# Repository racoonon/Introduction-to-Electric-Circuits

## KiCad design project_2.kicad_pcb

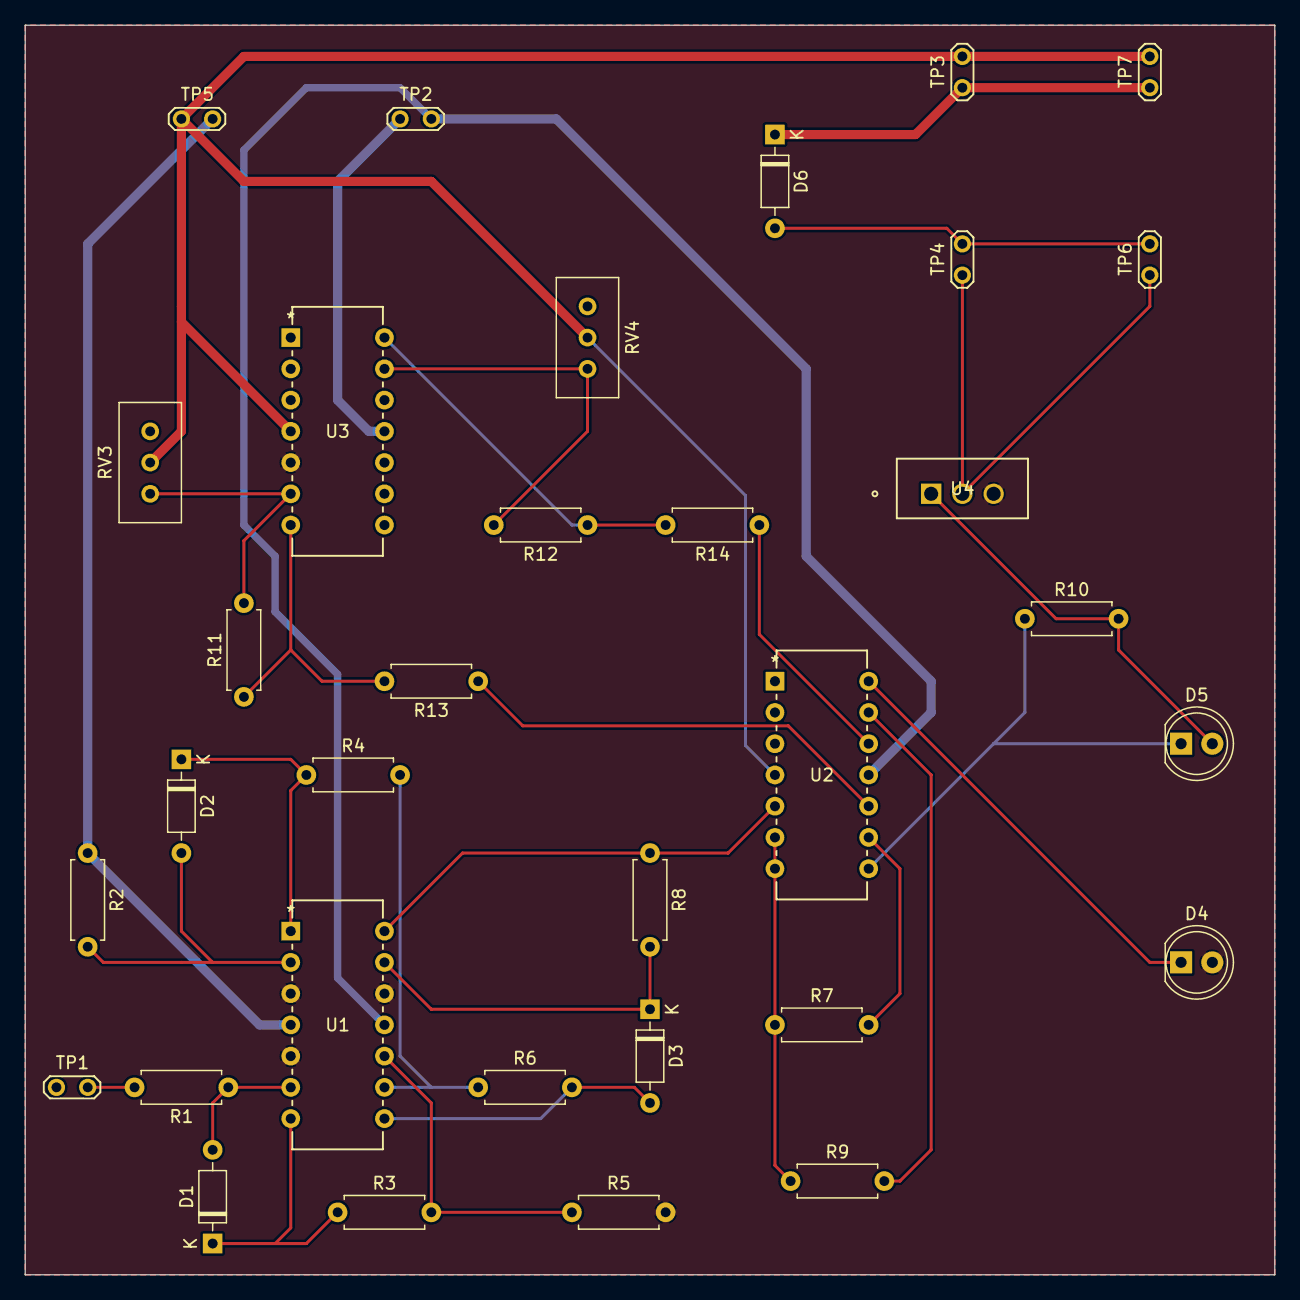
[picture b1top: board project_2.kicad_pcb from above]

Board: 2 copper layers, 101.6 x 101.6 mm, 33 parts (0 on the bottom side), 27 nets.

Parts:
D1, D2, D3, D6: 1N4148; D_DO-35_SOD27_P7.62mm_Horizontal
D4, D5: LED; LED_D5.0mm
R1, R2, R3, R4, R5, R7, R9, R10: 1.1k; R_Axial_DIN0207_L6.3mm_D2.5mm_P7.62mm_Horizontal
R6: 2.2k; R_Axial_DIN0207_L6.3mm_D2.5mm_P7.62mm_Horizontal
R8: 11k; R_Axial_DIN0207_L6.3mm_D2.5mm_P7.62mm_Horizontal
R11, R12, R13, R14: R; R_Axial_DIN0207_L6.3mm_D2.5mm_P7.62mm_Horizontal
RV3, RV4: R_Potentiometer; Potentiometer_Bourns_3296W_Vertical
TP1, TP2, TP3, TP4, TP5, TP6, TP7: TestPoint_2Pole; TestPoint_2Pads_Pitch2.54mm_Drill0.8mm
U1, U2, U3: LM324N; DIP-14_STM
U4: TIP120; TO-220_STM

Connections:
GND: D4.2 (A), R5.2, U1.3 (IN+), U1.5 (IN+), U1.12 (IN+), U3.5 (IN+), U4.3
unnamed: D1.2 (A), R1.1, U1.6 (IN-)
unnamed: D1.1 (K), R3.1, U1.7 (OUT)
unnamed: D2.2 (A), R2.2, U1.2 (IN-)
unnamed: D2.1 (K), R4.1, U1.1 (OUT)
unnamed: D3.2 (A), R6.2, U1.8 (OUT)
unnamed: D3.1 (K), R8.2, U1.13 (IN-)
unnamed: D4.1 (K), U2.14 (OUT)
unnamed: D5.2 (A), R10.2, U4.1
unnamed: D5.1 (K), R10.1, U2.8 (OUT)
unnamed: D6.2 (A), TP4.2, TP6.2
unnamed: D6.1 (K), TP3.1, TP7.1
unnamed: R1.2, TP1.2
unnamed: R3.2, R5.1, U1.10 (IN+)
unnamed: R4.2, R6.1, U1.9 (IN-)
unnamed: R7.1, R9.1, U2.6 (IN-), U2.7 (OUT)
unnamed: R7.2, U2.9 (IN-)
unnamed: R8.1, U1.14 (OUT), U2.5 (IN+)
unnamed: R9.2, U2.13 (IN-)
unnamed: R11.1, R13.2, U3.7 (OUT)
unnamed: R11.2, RV3.3, U3.6 (IN-)
unnamed: R13.1, U2.10 (IN+)
unnamed: R14.1, U2.12 (IN+)
unnamed: TP4.1, TP6.1, U4.2
unnamed: R2.1, TP5.2, U1.4 (V+)
unnamed: R12.1, R12.2, R14.2, RV4.1, RV4.3, TP2.1, TP2.2, U1.11 (V-), U2.11 (V-), U3.11 (V-), U3.12 (IN+), U3.13 (IN-), U3.14 (OUT)
unnamed: RV3.2, RV4.2, TP3.2, TP5.1, TP7.2, U2.4 (V+), U3.4 (V+)
